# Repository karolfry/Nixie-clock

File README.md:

# Nixie-clock-ESP32
My new nixie clock  project based on esp32 lolin lite and LC-516 nixie tubes

Main componnents:
-ESP32 lolin lite 
-Nixie lamps LC-516
-Nixie drivers 74141
-Scift registers 74HC595
-HV voltage converter

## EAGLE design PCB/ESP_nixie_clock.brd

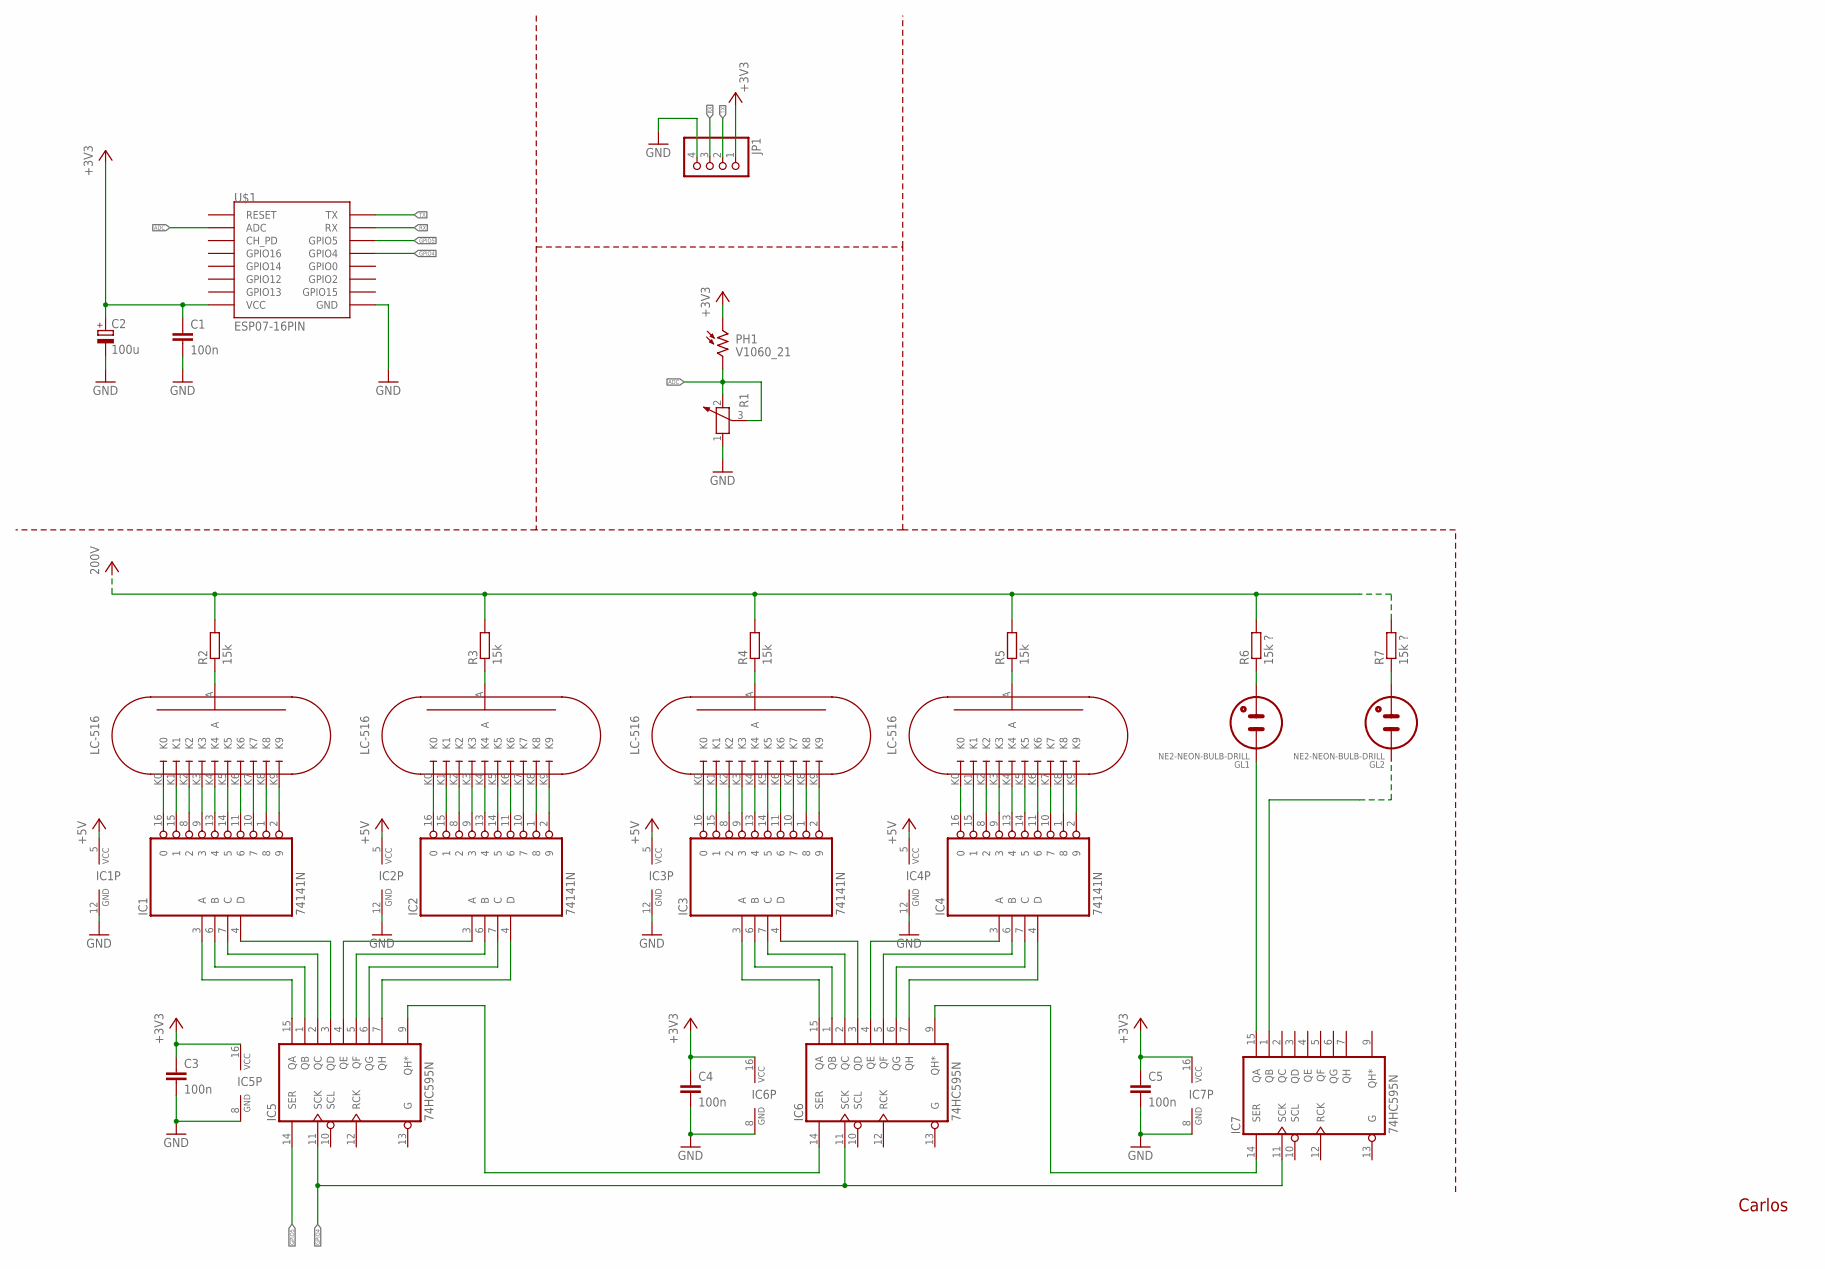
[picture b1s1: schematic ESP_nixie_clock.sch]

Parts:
C1, C3, C4, C5: 100n; C0805K
C2: 100u; 153CLV-0810
GL1, GL2: NE2-NEON-BULB-DRILL
IC1, IC2, IC3, IC4: 74141N; DIL16
IC5, IC6, IC7: 74HC595N; DIL16
JP1: PINHD-1X4/90; 1X04/90
PH1: V1060_21; TO-5_V10
R1: POTENTIOMETER_PT-10; PT-10
R2, R3, R4, R5: 15k; 0207/10
R6, R7: 15k ?; 0207/10
U$1: ESP07-16PIN
U$2, U$3, U$4, U$5: LC-516

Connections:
+3V3: C1.1, C2.+, C3.1, C4.1, C5.1, IC5.16 (VCC), IC6.16 (VCC), IC7.16 (VCC), JP1.1, PH1.1, U$1.VCC
+5V: IC1.5 (VCC), IC2.5 (VCC), IC3.5 (VCC), IC4.5 (VCC)
ADC: PH1.2, R1.2, R1.3, U$1.ADC
GND: C1.2, C2.-, C3.2, C4.2, C5.2, IC1.12 (GND), IC2.12 (GND), IC3.12 (GND), IC4.12 (GND), IC5.8 (GND), IC6.8 (GND), IC7.8 (GND), JP1.4, R1.1, U$1.GND
GPIO4: IC5.11 (SCK), IC6.11 (SCK), IC7.11 (SCK), U$1.GPIO5 (GPIO4)
GPIO5: IC5.14 (SER), U$1.GPIO4 (GPIO5)
unnamed: IC1.16 (0), U$2.K0
unnamed: IC1.15 (1), U$2.K1
unnamed: IC1.8 (2), U$2.K2
unnamed: IC1.9 (3), U$2.K3
unnamed: IC1.13 (4), U$2.K4
unnamed: IC1.11 (6), U$2.K6
unnamed: IC1.14 (5), U$2.K5
unnamed: IC1.10 (7), U$2.K7
unnamed: IC1.1 (8), U$2.K8
unnamed: IC1.2 (9), U$2.K9
unnamed: IC2.16 (0), U$3.K0
unnamed: IC2.15 (1), U$3.K1
unnamed: IC2.8 (2), U$3.K2
unnamed: IC2.9 (3), U$3.K3
unnamed: IC2.13 (4), U$3.K4
unnamed: IC2.14 (5), U$3.K5
unnamed: IC2.11 (6), U$3.K6
unnamed: IC2.10 (7), U$3.K7
unnamed: IC2.1 (8), U$3.K8
unnamed: IC2.2 (9), U$3.K9
unnamed: IC3.16 (0), U$4.K0
unnamed: IC3.15 (1), U$4.K1
unnamed: IC3.8 (2), U$4.K2
unnamed: IC3.9 (3), U$4.K3
unnamed: IC3.13 (4), U$4.K4
unnamed: IC3.14 (5), U$4.K5
unnamed: IC3.11 (6), U$4.K6
unnamed: IC3.10 (7), U$4.K7
unnamed: IC3.1 (8), U$4.K8
unnamed: IC3.2 (9), U$4.K9
unnamed: IC4.16 (0), U$5.K0
unnamed: IC4.15 (1), U$5.K1
unnamed: IC4.8 (2), U$5.K2
unnamed: IC4.9 (3), U$5.K3
unnamed: IC4.13 (4), U$5.K4
unnamed: IC4.14 (5), U$5.K5
unnamed: IC4.11 (6), U$5.K6
unnamed: IC4.10 (7), U$5.K7
unnamed: IC4.1 (8), U$5.K8
unnamed: IC4.2 (9), U$5.K9
unnamed: IC1.3 (A), IC5.15 (QA)
unnamed: IC1.6 (B), IC5.1 (QB)
unnamed: IC1.7 (C), IC5.2 (QC)
unnamed: IC1.4 (D), IC5.3 (QD)
unnamed: IC2.3 (A), IC5.4 (QE)
unnamed: IC2.6 (B), IC5.5 (QF)
unnamed: IC2.7 (C), IC5.6 (QG)
unnamed: IC2.4 (D), IC5.7 (QH)
unnamed: IC5.9 (QH*), IC6.14 (SER)
unnamed: IC3.3 (A), IC6.15 (QA)
unnamed: IC3.6 (B), IC6.1 (QB)
unnamed: IC3.7 (C), IC6.2 (QC)
unnamed: IC3.4 (D), IC6.3 (QD)
unnamed: IC4.3 (A), IC6.4 (QE)
unnamed: IC4.6 (B), IC6.5 (QF)
unnamed: IC4.7 (C), IC6.6 (QG)
unnamed: IC4.4 (D), IC6.7 (QH)
unnamed: IC6.9 (QH*), IC7.14 (SER)
unnamed: R2.1, U$2.A
unnamed: GL1.1 (A), IC7.15 (QA)
unnamed: GL2.1 (A), IC7.1 (QB)
unnamed: R3.1, U$3.A
unnamed: R4.1, U$4.A
unnamed: R5.1, U$5.A
unnamed: GL1.2 (A1), R6.1
unnamed: GL2.2 (A1), R7.1
RX: JP1.3, U$1.RX
TX: JP1.2, U$1.TX
VCC: R2.2, R3.2, R4.2, R5.2, R6.2, R7.2

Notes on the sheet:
Carlos

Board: 2 copper layers, 28 parts (0 on the bottom side), 75 nets, no tracks yet.

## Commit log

2019-12-22 Add draft version of schematic, modified README, add datasheet
2021-04-15 pcb update
2021-04-15 Add software project
2021-04-15 update README file
2021-04-24 redme update
